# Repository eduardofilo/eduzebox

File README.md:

# EdUzebox

Uzebox clone with SCART connector (RGB output) and most SMD components.

https://apuntes.eduardofilo.es/2020-02-08-eduzebox.html

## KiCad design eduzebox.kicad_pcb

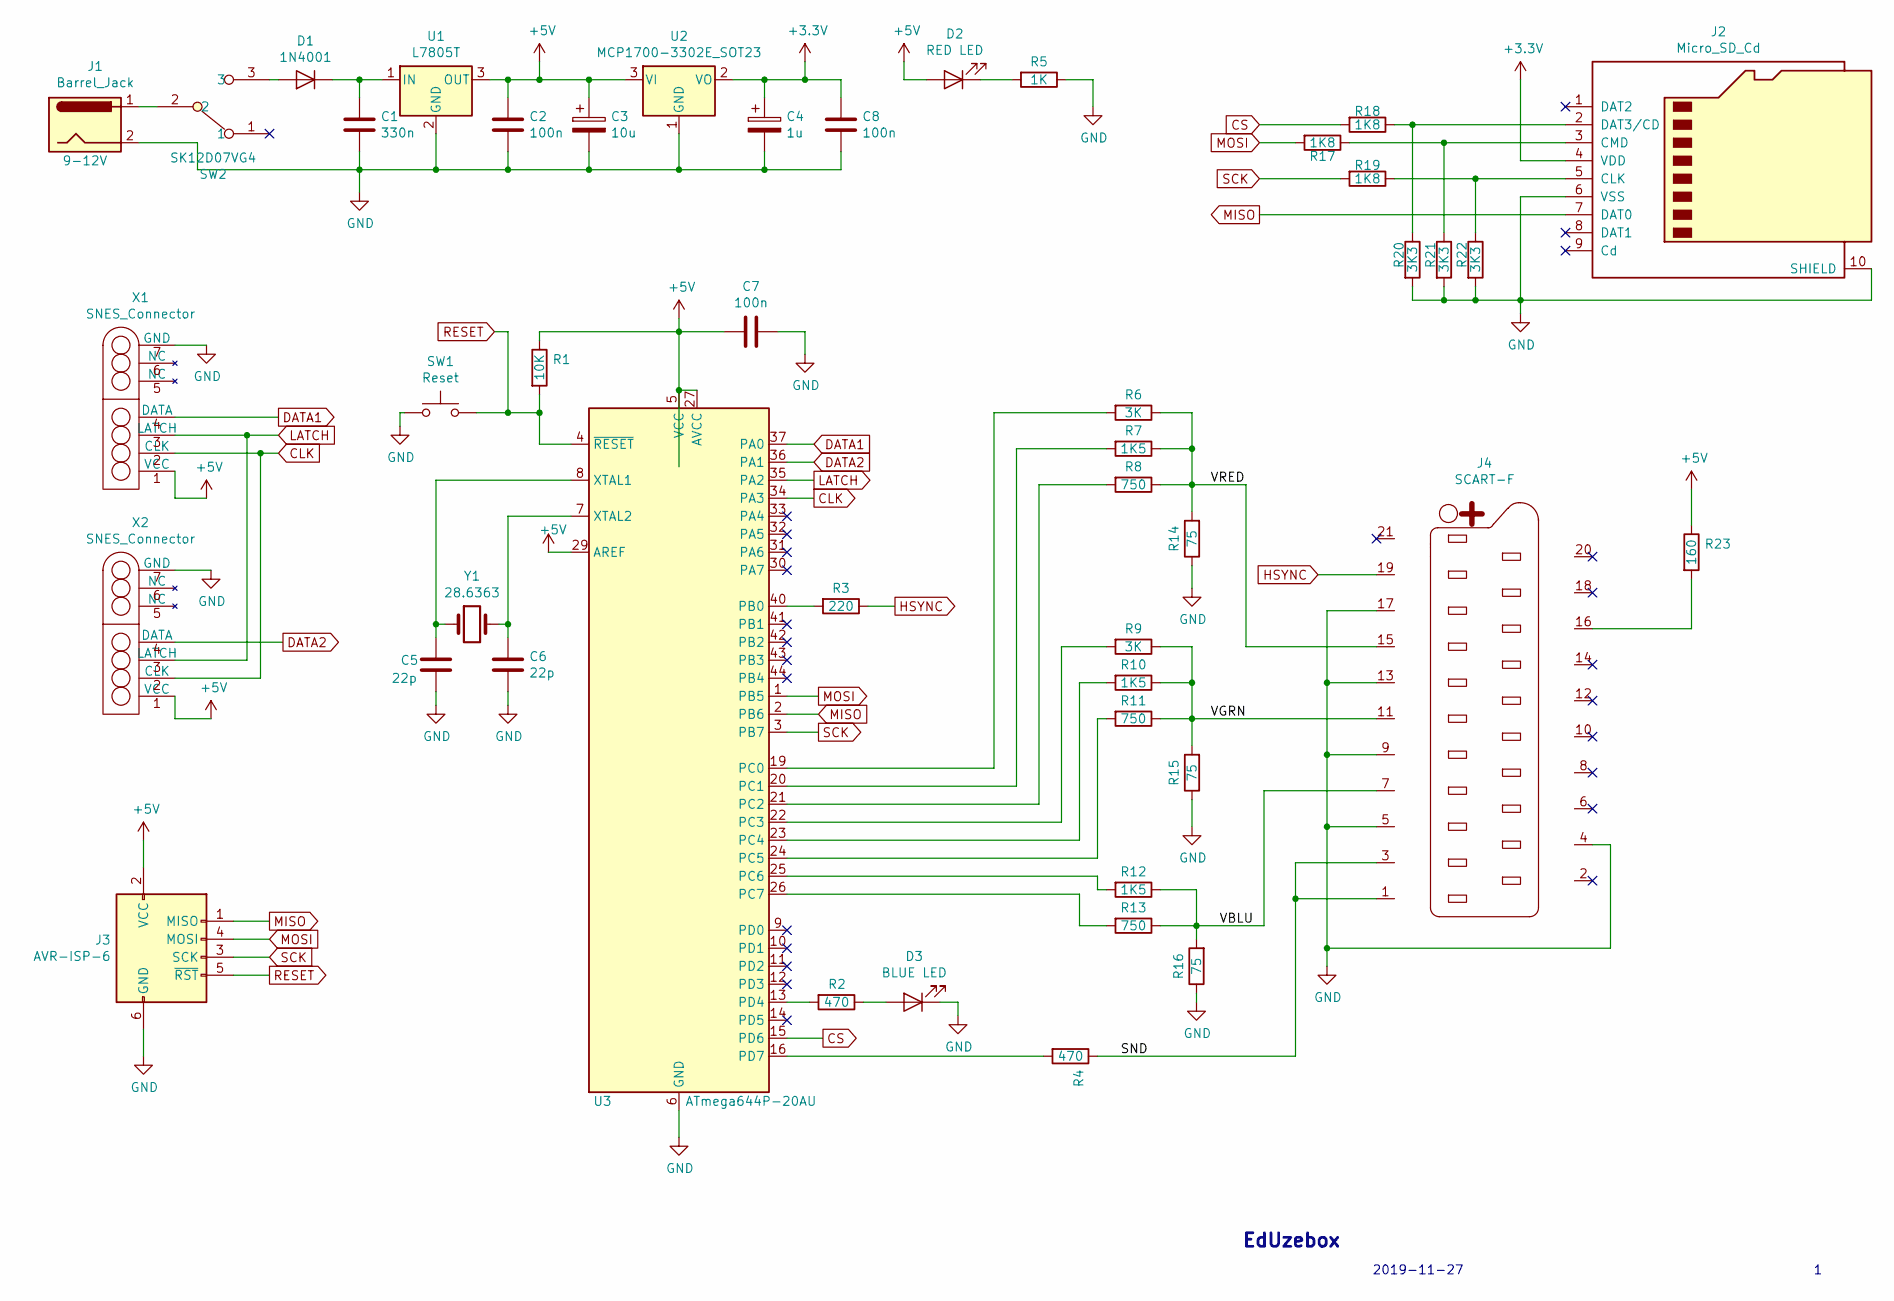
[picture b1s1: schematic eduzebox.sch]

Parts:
C1: 330n; C_0805_2012Metric_Pad1.15x1.40mm_HandSolder
C2, C7, C8: 100n; C_0805_2012Metric_Pad1.15x1.40mm_HandSolder
C3: 10u; CP_EIA-3216-18_Kemet-A_Pad1.58x1.35mm_HandSolder
C4: 1u; CP_EIA-3216-18_Kemet-A_Pad1.58x1.35mm_HandSolder
C5, C6: 22p; C_0805_2012Metric_Pad1.15x1.40mm_HandSolder
D1: 1N4001; D_SOD-123F
D2: RED LED; LED_D5.0mm
D3: BLUE LED; LED_D5.0mm
J1: Barrel_Jack; BarrelJack_Wuerth_6941xx301002
J2: Micro_SD_Cd
J3: AVR-ISP-6; PinHeader_2x03_P2.54mm_Vertical
J4: SCART-F; SCART
R1: 10K; R_0805_2012Metric_Pad1.15x1.40mm_HandSolder
R2, R4: 470; R_0805_2012Metric_Pad1.15x1.40mm_HandSolder
R3: 220; R_0805_2012Metric_Pad1.15x1.40mm_HandSolder
R5: 1K; R_0805_2012Metric_Pad1.15x1.40mm_HandSolder
R6, R9: 3K; R_0805_2012Metric_Pad1.15x1.40mm_HandSolder
R7, R10, R12: 1K5; R_0805_2012Metric_Pad1.15x1.40mm_HandSolder
R8, R11, R13: 750; R_0805_2012Metric_Pad1.15x1.40mm_HandSolder
R14, R15, R16: 75; R_0805_2012Metric_Pad1.15x1.40mm_HandSolder
R17, R18, R19: 1K8; R_0805_2012Metric_Pad1.15x1.40mm_HandSolder
R20, R21, R22: 3K3; R_0805_2012Metric_Pad1.15x1.40mm_HandSolder
R23: 160; R_0805_2012Metric_Pad1.15x1.40mm_HandSolder
SW1: Reset; SW_Push_1P1T_NO_6x6mm_H9.5mm
SW2: SK12D07VG4; SW_CuK_OS102011MA1QN1_SPDT_Angled
U1: L7805T; TO-220-3_Vertical
U2: MCP1700-3302E_SOT23; SOT-23
U3: ATmega644P-20AU; TQFP-44_10x10mm_P0.8mm
X1, X2: SNES_Connector; SNES
Y1: 28.6363; Crystal_HC49-4H_Vertical

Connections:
+3V3: C4.1, C8.1, J2.4 (VDD), U2.2 (VO)
+5V: C2.1, C3.1, C7.2, D2.2 (A), J3.2 (VCC), R1.1, R23.1, U1.3 (OUT), U2.3 (VI), U3.5 (VCC), U3.17 (VCC), U3.27 (AVCC), U3.29 (AREF), U3.38 (VCC), X1.1 (VCC), X2.1 (VCC)
/SND: J4.1, J4.3, R4.1
/VBLU: J4.7, R12.1, R13.1, R16.2
/VGRN: J4.11, R9.1, R10.1, R11.1, R15.2
/VRED: J4.15, R6.1, R7.1, R8.1, R14.2
CLK: U3.34 (PA3), X1.2 (CLK), X2.2 (CLK)
CS: R18.2, U3.15 (PD6)
DATA1: U3.37 (PA0), X1.4 (DATA)
DATA2: U3.36 (PA1), X2.4 (DATA)
GND: C1.2, C2.2, C3.2, C4.2, C5.2, C6.2, C7.1, C8.2, D3.1 (K), J1.2, J2.6 (VSS), J2.10 (SHIELD), J3.6 (GND), J4.4, J4.5, J4.9, J4.13, J4.17, R5.1, R14.1, R15.1, R16.1, R20.2, R21.2, R22.2, SW1.1, U1.2 (GND), U2.1 (GND), U3.6 (GND), U3.18 (GND), U3.28 (GND), U3.39 (GND), X1.7 (GND), X2.7 (GND)
HSYNC: J4.19, R3.1
LATCH: U3.35 (PA2), X1.3 (LATCH), X2.3 (LATCH)
MISO: J2.7 (DAT0), J3.1 (MISO), U3.2 (PB6)
MOSI: J3.4 (MOSI), R17.2, U3.1 (PB5)
unnamed: C1.1, D1.1 (K), U1.1 (IN)
unnamed: C5.1, U3.8 (XTAL1), Y1.1
unnamed: C6.1, U3.7 (XTAL2), Y1.2
unnamed: D1.2 (A), SW2.3
unnamed: D2.1 (K), R5.2
unnamed: D3.2 (A), R2.1
unnamed: J1.1, SW2.2
unnamed: J2.2 (DAT3/CD), R18.1, R20.1
unnamed: J2.3 (CMD), R17.1, R21.1
unnamed: J2.5 (CLK), R19.1, R22.1
unnamed: J4.16, R23.2
unnamed: R2.2, U3.13 (PD4)
unnamed: R3.2, U3.40 (PB0)
unnamed: R4.2, U3.16 (PD7)
unnamed: R6.2, U3.19 (PC0)
unnamed: R7.2, U3.20 (PC1)
unnamed: R8.2, U3.21 (PC2)
unnamed: R9.2, U3.22 (PC3)
unnamed: R10.2, U3.23 (PC4)
unnamed: R11.2, U3.24 (PC5)
unnamed: R12.2, U3.25 (PC6)
unnamed: R13.2, U3.26 (PC7)
RESET: J3.5 (~RST), R1.2, SW1.2, U3.4 (~RESET)
SCK: J3.3 (SCK), R19.2, U3.3 (PB7)

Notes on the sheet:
EdUzebox
2019-11-27

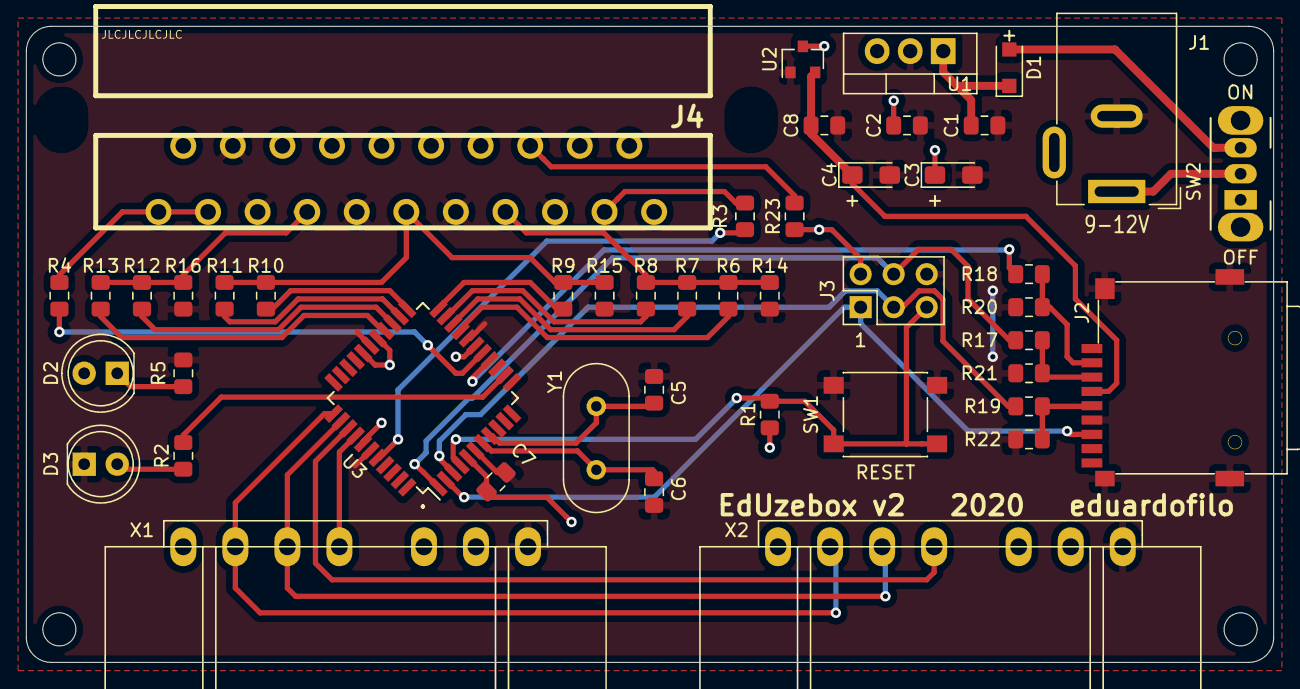
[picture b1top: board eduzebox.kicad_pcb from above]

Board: 2 copper layers, 95.9 x 48.9 mm, 46 parts (0 on the bottom side), 39 nets.

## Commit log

2020-02-04 First commit.
2020-02-15 Se incorpora el 7805 a la hoja BOM.
2020-08-08 Añadidos tornillos a BOM.
2020-08-08 Ficheros de la carcasa (FreeCAD y STLs).
2020-08-09 Enlace a post de proyecto en README.
2020-09-27 HTTPS link.
